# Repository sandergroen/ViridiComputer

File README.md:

# ViridiComputer
W65C02 based 8-bit computer

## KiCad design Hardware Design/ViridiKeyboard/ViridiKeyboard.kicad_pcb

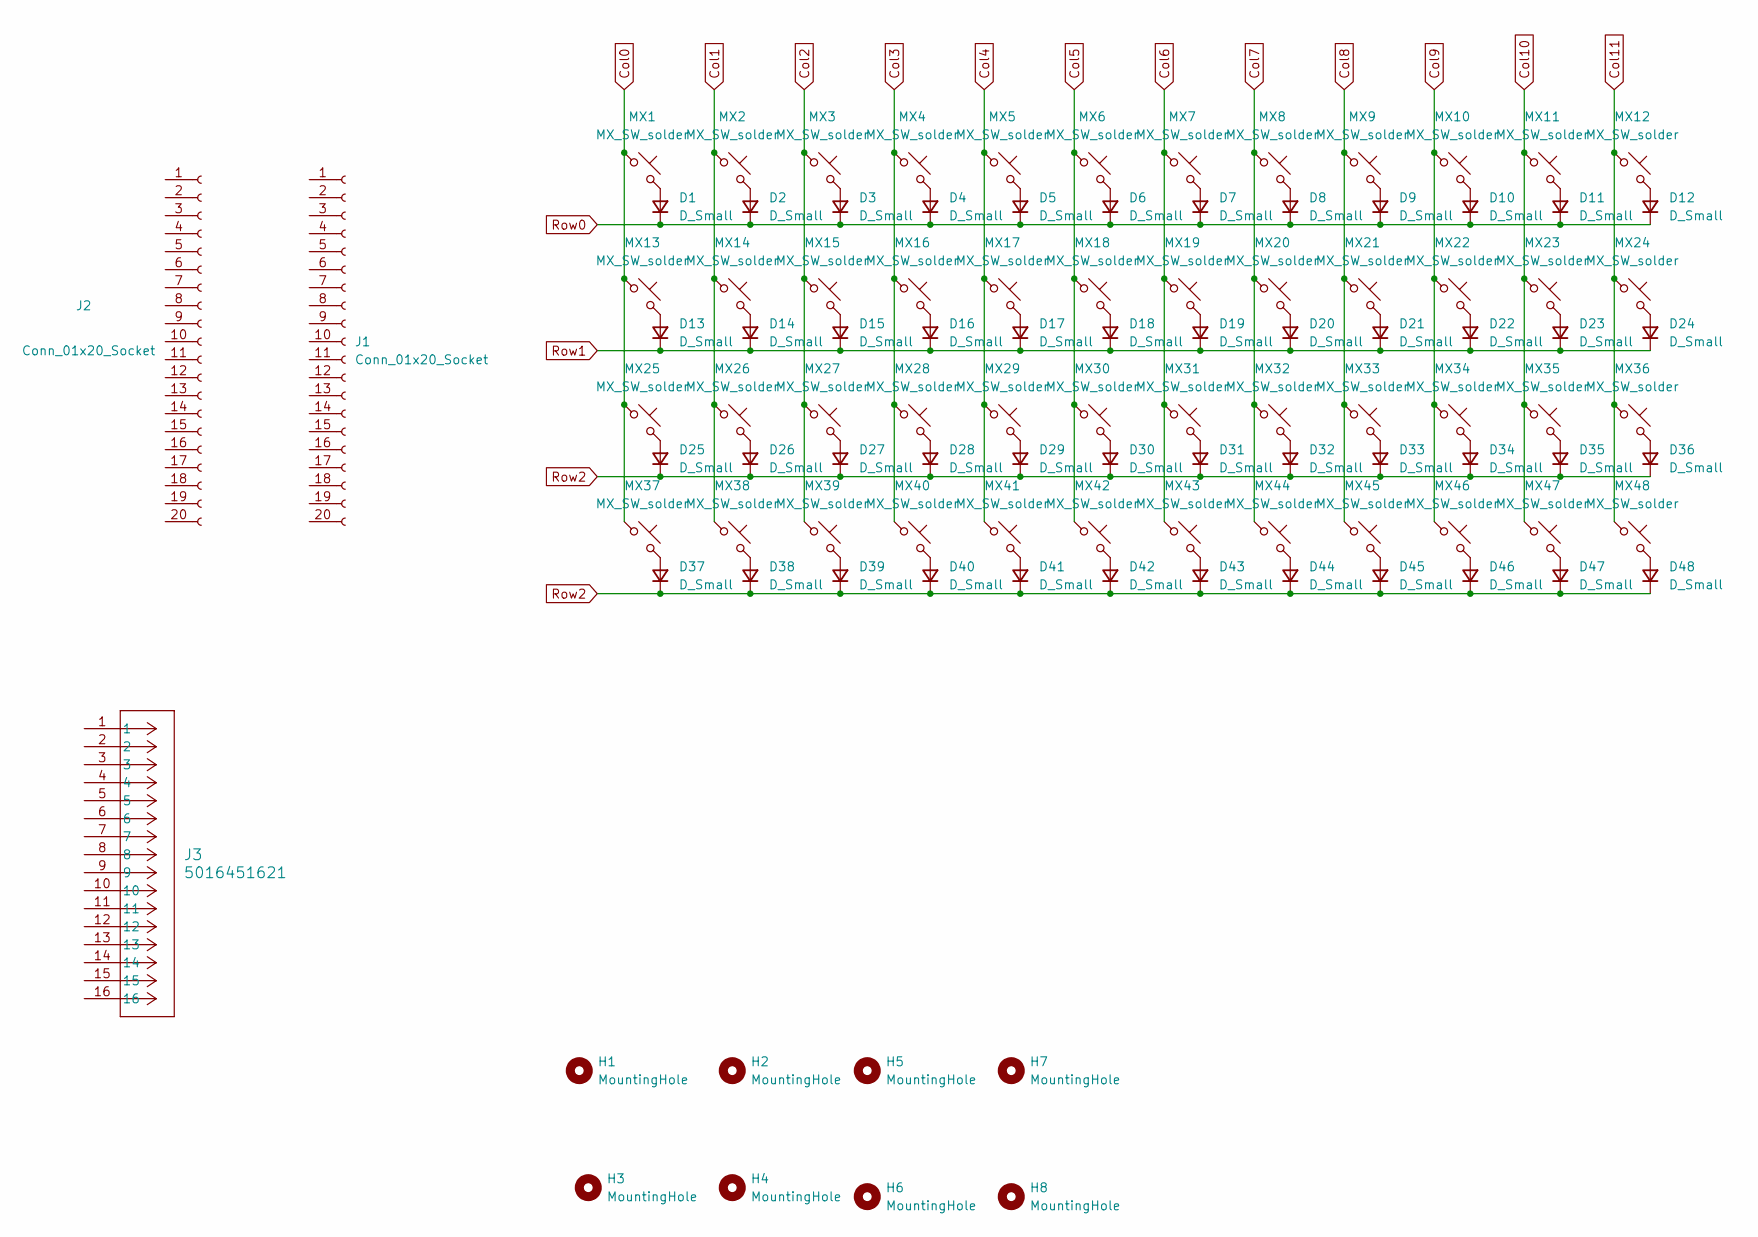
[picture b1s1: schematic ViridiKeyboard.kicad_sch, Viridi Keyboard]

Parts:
D1, D2, D3, D4, D5, D6, D7, D8, D9, D10, D11, D12, D13, D14, D15, D16, D17, D18, D19, D20, D21, D22, D23, D24, D25, D26, D27, D28, D29, D30, D31, D32, D33, D34, D35, D36, D37, D38, D39, D40, D41, D42, D43, D44, D45, D46, D47, D48: D_Small; D_SOD-123
H1, H2, H3, H4, H5, H6, H7, H8: MountingHole; MountingHole_2.5mm
J1, J2: Conn_01x20_Socket; PinSocket_1x20_P2.54mm_Vertical
J3: 5016451621; CON_5016451621_MOL
MX1, MX2, MX3, MX4, MX5, MX6, MX7, MX8, MX9, MX10, MX11, MX12, MX13, MX14, MX15, MX16, MX17, MX18, MX19, MX20, MX21, MX22, MX23, MX24, MX25, MX26, MX27, MX28, MX29, MX30, MX31, MX32, MX33, MX34, MX35, MX36, MX37, MX38, MX39, MX40, MX41, MX42, MX43, MX44, MX45, MX46, MX47, MX48: MX_SW_solder; SW_MX_1u

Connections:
Col0: MX1.1, MX13.1, MX25.1, MX37.1
Col1: MX2.1, MX14.1, MX26.1, MX38.1
Col2: MX3.1, MX15.1, MX27.1, MX39.1
Col3: MX4.1, MX16.1, MX28.1, MX40.1
Col4: MX5.1, MX17.1, MX29.1, MX41.1
Col5: MX6.1, MX18.1, MX30.1, MX42.1
Col6: MX7.1, MX19.1, MX31.1, MX43.1
Col7: MX8.1, MX20.1, MX32.1, MX44.1
Col8: MX9.1, MX21.1, MX33.1, MX45.1
Col9: MX10.1, MX22.1, MX34.1, MX46.1
Col10: MX11.1, MX23.1, MX35.1, MX47.1
Col11: MX12.1, MX24.1, MX36.1, MX48.1
unnamed: D1.2 (A), MX1.2
unnamed: D2.2 (A), MX2.2
unnamed: D3.2 (A), MX3.2
unnamed: D4.2 (A), MX4.2
unnamed: D5.2 (A), MX5.2
unnamed: D6.2 (A), MX6.2
unnamed: D7.2 (A), MX7.2
unnamed: D8.2 (A), MX8.2
unnamed: D9.2 (A), MX9.2
unnamed: D10.2 (A), MX10.2
unnamed: D11.2 (A), MX11.2
unnamed: D12.2 (A), MX12.2
unnamed: D13.2 (A), MX13.2
unnamed: D14.2 (A), MX14.2
unnamed: D15.2 (A), MX15.2
unnamed: D16.2 (A), MX16.2
unnamed: D17.2 (A), MX17.2
unnamed: D18.2 (A), MX18.2
unnamed: D19.2 (A), MX19.2
unnamed: D20.2 (A), MX20.2
unnamed: D21.2 (A), MX21.2
unnamed: D22.2 (A), MX22.2
unnamed: D23.2 (A), MX23.2
unnamed: D24.2 (A), MX24.2
unnamed: D25.2 (A), MX25.2
unnamed: D26.2 (A), MX26.2
unnamed: D27.2 (A), MX27.2
unnamed: D28.2 (A), MX28.2
unnamed: D29.2 (A), MX29.2
unnamed: D30.2 (A), MX30.2
unnamed: D31.2 (A), MX31.2
unnamed: D32.2 (A), MX32.2
unnamed: D33.2 (A), MX33.2
unnamed: D34.2 (A), MX34.2
unnamed: D35.2 (A), MX35.2
unnamed: D36.2 (A), MX36.2
unnamed: D37.2 (A), MX37.2
unnamed: D38.2 (A), MX38.2
unnamed: D39.2 (A), MX39.2
unnamed: D40.2 (A), MX40.2
unnamed: D41.2 (A), MX41.2
unnamed: D42.2 (A), MX42.2
unnamed: D43.2 (A), MX43.2
unnamed: D44.2 (A), MX44.2
unnamed: D45.2 (A), MX45.2
unnamed: D46.2 (A), MX46.2
unnamed: D47.2 (A), MX47.2
unnamed: D48.2 (A), MX48.2
Row0: D1.1 (K), D2.1 (K), D3.1 (K), D4.1 (K), D5.1 (K), D6.1 (K), D7.1 (K), D8.1 (K), D9.1 (K), D10.1 (K), D11.1 (K), D12.1 (K)
Row1: D13.1 (K), D14.1 (K), D15.1 (K), D16.1 (K), D17.1 (K), D18.1 (K), D19.1 (K), D20.1 (K), D21.1 (K), D22.1 (K), D23.1 (K), D24.1 (K)
Row2: D25.1 (K), D26.1 (K), D27.1 (K), D28.1 (K), D29.1 (K), D30.1 (K), D31.1 (K), D32.1 (K), D33.1 (K), D34.1 (K), D35.1 (K), D36.1 (K), D37.1 (K), D38.1 (K), D39.1 (K), D40.1 (K), D41.1 (K), D42.1 (K), D43.1 (K), D44.1 (K), D45.1 (K), D46.1 (K), D47.1 (K), D48.1 (K)

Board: 2 copper layers, 107 parts (51 on the bottom side), 63 nets, no tracks yet.

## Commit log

2023-07-20 Initial Keyboard design
